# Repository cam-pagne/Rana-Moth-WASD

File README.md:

# The Rana Labs Moth (WASD Version)

WASD version of [Rana Labs'](https://github.com/rana-sylvatica) Moth, a foldable leverless controller.

<div style="display: flex;">
    
</div>

---

## Build Overview (What do I need to make one?)

I printed the entire shell, hinges, etc., in **Bambu Lab Matte PLA** (though any PLA should work, build quality feel may vary).

- **Mainboards:** RP2040—**integrated directly onto the left custom PCB.** The right side is connnected by ribbon cable.
- **Switches:** Must be **low profile switches.** I use pretty much any Kailh Choc Low Profile switches. They all work, just choose a preferred switch type.
- **USB-C Connector:** [Quark's](https://github.com/quark-works) and Rana Labs' [QuRB](https://github.com/rana-sylvatica/rana-tadpole/tree/main/PCBs/Breakout%20Board%20(QuRB)), a USB C Breakout board with a ribbon cable port, for solderless assembly.
- **Hardware:** M2 screws and M3 screws are the only fasteners required to assemble. You will need **ten M3 heat inserts** for the backplates, **twelve M3 x 5/6mm bolts** for the backplates and QuRB, and **eight M2 x 4mm bolts** to secure each half of the mainboards.

---

## Assembly

### PCB

To streamline your build, I’ve designed a custom PCB for this controller. This board integrates the Pico directly eliminating the need for any handwiring of the microcontroller. The **only soldering required is the installation of the hotswap sockets for the Choc switches.**

The two halves of the board are connected using a 20 pin, .5 pitch ribbon cable, and the QuRB is connected to the Left side board for USB C port via a 12 pin, .5 pitch ribbon cable.

---

## Magnets

Strong magnets are crucial, as they must counteract every spring in your switches. I used:

- **6x3mm Neodymium magnets**, stacked **2 high** in each of the **10 total holes** (20 magnets overall).
- This setup creates a satisfying snap and keeps the Moth securely folded.

**Amazon link:** [Magnets used](https://www.amazon.com/dp/B096LZNZTQ?ref=cm_sw_r_cp_ud_dp_ZEAK3BD945P57Y9BB6P4&ref_=cm_sw_r_cp_ud_dp_ZEAK3BD945P57Y9BB6P4&social_share=cm_sw_r_cp_ud_dp_ZEAK3BD945P57Y9BB6P4&skipTwisterOG=1&newOGT=1&th=1)

---

## 'Prism' Ergonomic Mode

For the reverse folded position:

- A **lip** on the two hinge pieces prevents overfolding by creating a defined stopping point.
- The rounded back of the hinges generates friction, ensuring rigidity in the ergonomic 'prism' configuration.

### Adjustments:

- The hinge lip’s width can be edited to modify the folding angle.

---

## Miscellaneous Notes

- **Button Fit:** Ensure buttons sit flush with the face surface when pressed to allow proper folding.
- **Magnet Strength:** Although strong neodymium magnets can overcome minor misalignments, aim for a flush fit.
- **Hinge Pin Slot:** While you can add caps for a cleaner look, the friction fit alone holds securely.

---

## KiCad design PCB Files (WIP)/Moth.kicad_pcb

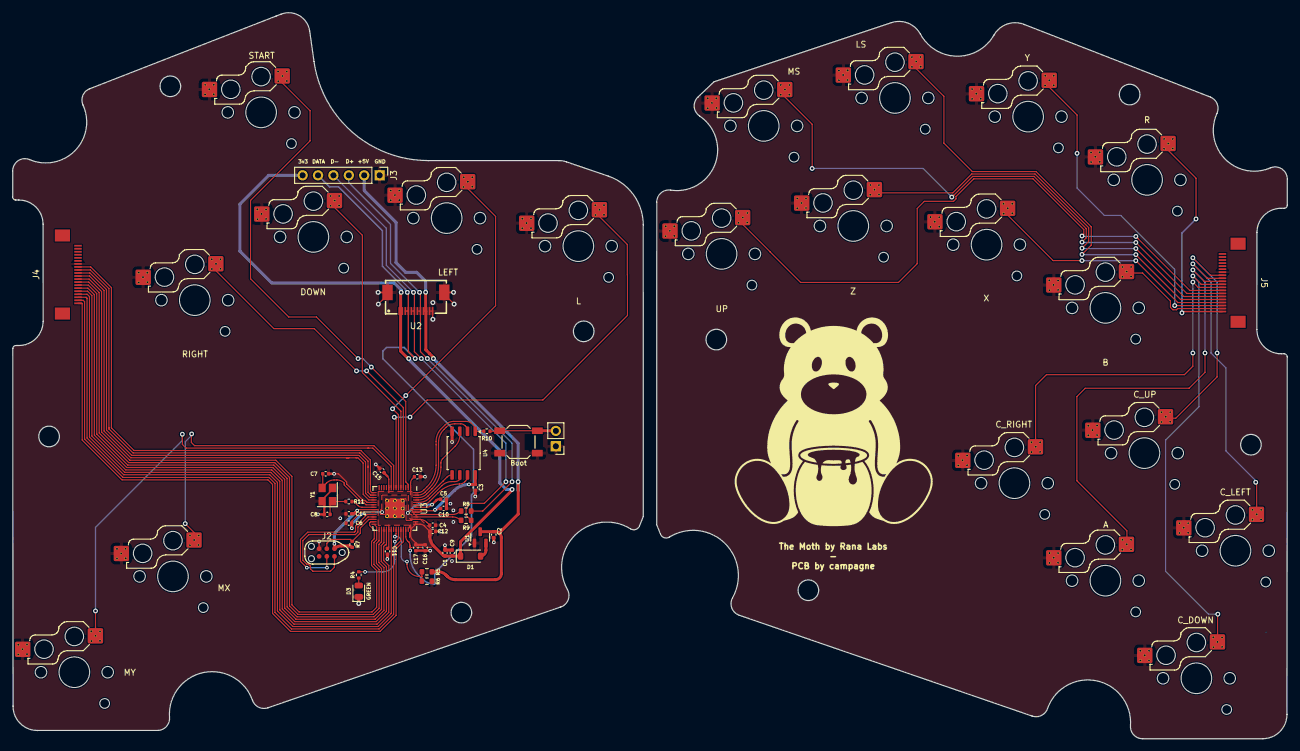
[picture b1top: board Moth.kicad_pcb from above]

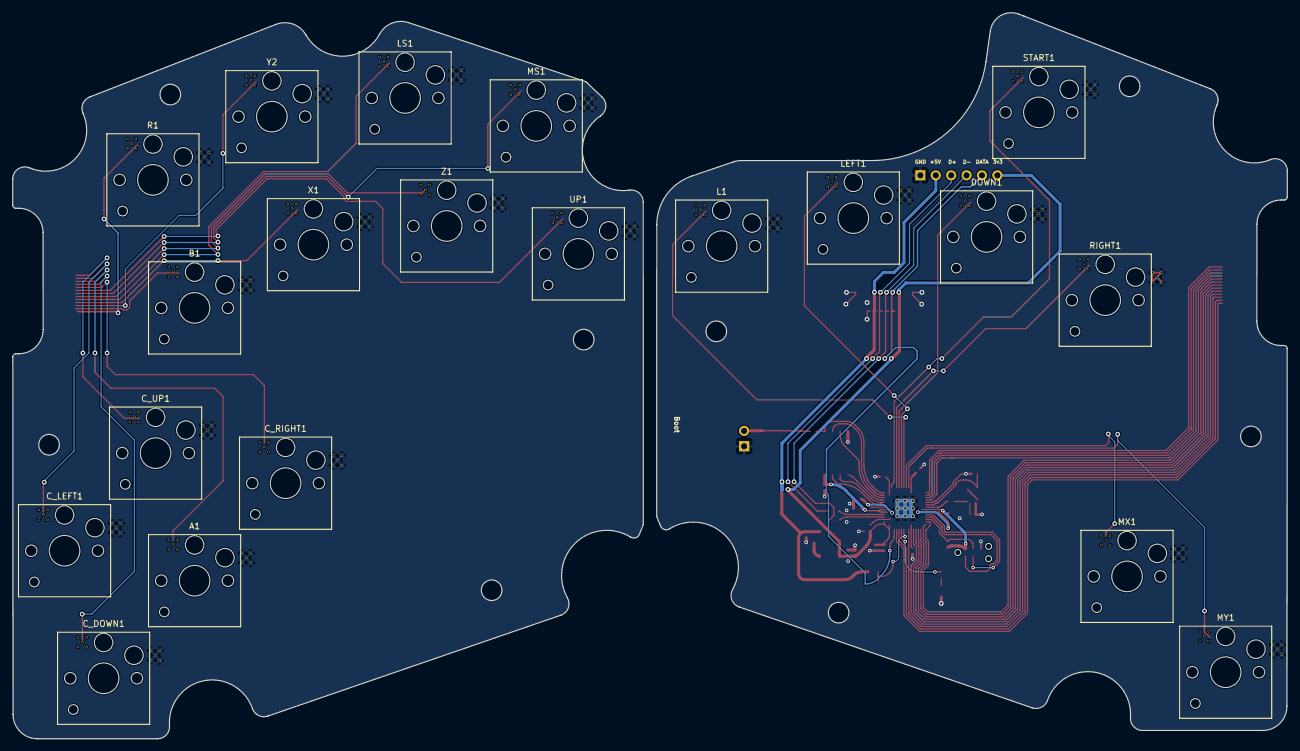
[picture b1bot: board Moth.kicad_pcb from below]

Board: 2 copper layers, 210.2 x 119.7 mm, 58 parts (20 on the bottom side), 59 nets.

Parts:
A1: A; SW_Hotswap_Kailh_Choc_V1V2_THT
B1: B; SW_Hotswap_Kailh_Choc_V1V2_THT
C1, C2, C4, C10: 1uF; C_0402_1005Metric
C3, C5, C6, C11, C12, C13, C14, C15, C16, C17: 100nF; C_0402_1005Metric
C7, C8: 22pF; C_0402_1005Metric
C9: 10uF; C_0402_1005Metric
C_DOWN1: C Down; SW_Hotswap_Kailh_Choc_V1V2_THT
C_LEFT1: C Left; SW_Hotswap_Kailh_Choc_V1V2_THT
C_RIGHT1: C Right; SW_Hotswap_Kailh_Choc_V1V2_THT
C_UP1: C Up; SW_Hotswap_Kailh_Choc_V1V2_THT
D1: Schottky Diode; D_SOD-123
D3: GREEN; LED_0805_2012Metric
DOWN1: Down; SW_Hotswap_Kailh_Choc_V1V2_THT
J1: Conn_01x02; PinHeader_1x02_P2.54mm_Vertical
J2: JTAG_TC2030; CON_TC2030_outlined
J3: DuPont Connector; PinHeader_1x06_P2.54mm_Vertical
J4: Left Ribbon; FPC-05F-30PH20
J5: Right Ribbon; FPC-05F-30PH20
L1: L; SW_Hotswap_Kailh_Choc_V1V2_THT
LEFT1: Left; SW_Hotswap_Kailh_Choc_V1V2_THT
LS1: LS; SW_Hotswap_Kailh_Choc_V1V2_THT
MS1: MS; SW_Hotswap_Kailh_Choc_V1V2_THT
MX1: MX; SW_Hotswap_Kailh_Choc_V1V2_THT
MY1: MY; SW_Hotswap_Kailh_Choc_V1V2_THT
R1: R; SW_Hotswap_Kailh_Choc_V1V2_THT
R4: 470; R_0402_1005Metric
R5: 5.6k; R_0603_1608Metric
R6: 10k; R_0603_1608Metric
R7: 10k; R_0402_1005Metric
R8, R9: 27; R_0603_1608Metric
R10, R11: 1k; R_0402_1005Metric
RIGHT1: Right; SW_Hotswap_Kailh_Choc_V1V2_THT
START1: Start; SW_Hotswap_Kailh_Choc_V1V2_THT
SW1: Boot; SW_SPST_SKQG_WithStem
U1: XC6206; SOT-23
U2: X05A26H12G; FPC-SMD_X05A26H12G
U3: RP2040; RP2040-QFN-56
U4: W25Q128JVS; SOIC-8_5.23x5.23mm_P1.27mm
UP1: Up; SW_Hotswap_Kailh_Choc_V1V2_THT
X1: X; SW_Hotswap_Kailh_Choc_V1V2_THT
Y1: 12MHz; Crystal_SMD_3225-4Pin_3.2x2.5mm
Y2: Y; SW_Hotswap_Kailh_Choc_V1V2_THT
Z1: Z; SW_Hotswap_Kailh_Choc_V1V2_THT

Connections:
3vDiode: C1.2, C3.1, C9.1, C10.1, C11.1, C12.1, C13.1, C14.1, C15.1, C16.1, C17.1, D1.1 (K), J2.1 (VCC), J3.6, R7.1, U2.1, U2.2, U3.1 (IOVDD), U3.10 (IOVDD), U3.22 (IOVDD), U3.33 (IOVDD), U3.42 (IOVDD), U3.43 (ADC_AVDD), U3.44 (VREG_VIN), U3.48 (USB_VDD), U3.49 (IOVDD), U4.8 (VCC)
+1V1: C4.1, C5.1, C6.1, U3.23 (DVDD), U3.45 (VREG_VOUT), U3.50 (DVDD)
+5V: C2.2, J3.2, R5.1, U1.3 (VI), U2.9, U2.10
/D_+: R8.2, U3.47 (D+)
/D_-: R9.2, U3.46 (D-)
/XTAL_O: C8.2, R11.1, Y1.1
/~USB_BOOT: J1.2, R10.1, SW1.2
A: A1.1, J5.11
A RIBBON: J4.10, U3.17 (GPIO14)
B: B1.1, J5.2
B RIBBON: J4.19, U3.38 (GPIO26/ADC0)
CS: R10.2, U3.56 (QSPI_SS_N), U4.1 (~CS)
C_DN: C_DOWN1.1, J5.10
C_DN RIBBON: J4.11, U3.18 (GPIO15)
C_LT: C_LEFT1.1, J5.12
C_LT RIBBON: J4.9, U3.16 (GPIO13)
C_RT: C_RIGHT1.1, J5.9
C_RT RIBBON: J4.12, U3.27 (GPIO16)
C_UP: C_UP1.1, J5.13
C_UP RIBBON: J4.8, U3.15 (GPIO12)
D+: J3.3, R8.1, U2.7, U2.8
D-: J3.4, R9.1, U2.5, U2.6
DATA: J3.5, U2.3, U2.4, U3.40 (GPIO28/ADC2)
DOWN: DOWN1.1, U3.5 (GPIO3)
GND: A1.2, B1.2, C1.1, C2.1, C3.2, C4.2, C5.2, C6.2, C7.1, C8.1, C9.2, C10.2, C11.2, C12.2, C13.2, C14.2, C15.2, C16.2, C17.2, C_DOWN1.2, C_LEFT1.2, C_RIGHT1.2, C_UP1.2, D3.1 (K), DOWN1.2, J1.1, J2.5 (GND), J3.1, J4.7, J5.14, L1.2, LEFT1.2, LS1.2, MS1.2, MX1.2, MY1.2, R1.2, R6.2, RIGHT1.2, START1.2, SW1.1, U1.1 (GND), U2.11, U2.12, U2.13, U2.14, U3.19 (TESTEN), U3.57 (GND), U4.4 (GND), UP1.2, X1.2, Y1.2, Y1.4, Y2.2, Z1.2
L: L1.1, U3.7 (GPIO5)
LEFT: LEFT1.1, U3.6 (GPIO4)
LS: J5.5, LS1.1
LS RIBBON: J4.16, U3.31 (GPIO20)
M1: MX1.1, U3.8 (GPIO6)
M2: MY1.1, U3.9 (GPIO7)
MS: J5.7, MS1.1
MS RIBBON: J4.14, U3.29 (GPIO18)
unnamed: D1.2 (A), U1.2 (VO)
unnamed: D3.2 (A), R4.2
PICO_LED: R4.1, U3.37 (GPIO25)
QSPI_CLK: U3.52 (QSPI_SCLK), U4.6 (CLK)
R: J5.1, R1.1
R RIBBON: J4.20, U3.39 (GPIO27/ADC1)
RIGHT: RIGHT1.1, U3.4 (GPIO2)
SD0: U3.53 (QSPI_SD0), U4.5 (DI(IO0))
SD1: U3.55 (QSPI_SD1), U4.2 (DO(IO1))
SD2: U3.54 (QSPI_SD2), U4.3 (IO2)
SD3: U3.51 (QSPI_SD3), U4.7 (IO3)
START: START1.1, U3.2 (GPIO0)
SWCLK: J2.4 (SWCLK), U3.24 (SWCLK)
SWD: J2.2 (SWDIO), U3.25 (SWDIO)
UP: J5.8, UP1.1
UP RIBBON: J4.13, U3.28 (GPIO17)
VBUS_SENSE: R5.2, R6.1, U3.36 (GPIO24)
X: J5.4, X1.1
X RIBBON: J4.17, U3.32 (GPIO21)
XTAL_IN: C7.2, U3.20 (XTAL_IN), Y1.3
XTAL_OUT: R11.2, U3.21 (XTAL_OUT)
Y: J5.3, Y2.1
Y RIBBON: J4.18, U3.34 (GPIO22)
Z: J5.6, Z1.1
Z RIBBON: J4.15, U3.30 (GPIO19)
~RESET: J2.3 (~RST), R7.2, U3.26 (~RUN)

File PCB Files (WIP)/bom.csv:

Designator,Footprint,Quantity,Value,LCSC Part #
"C1, C10, C2, C4",402,4,1uF,C52923
"C11, C12, C13, C14, C15, C16, C17, C3, C5, C6",402,10,100nF,C1525
"C7, C8",402,2,22pF,C1555
C9,402,1,10uF,C15525
D1,D_SOD-123,1,Schottky Diode,C8598
D3,805,1,RED,C84256
"R10, R11",402,2,1k,C11702
R4,402,1,470,C25117
R5,603,1,5.6k,C23189
R6,603,1,10k,C25804
R7,402,1,10k,C25744
"R8, R9",RP2040-QFN-56,2,27,C25190
SW1,SW_SPST_SKQG_WithStem,1,Boot,C318884 
U1,SOT-23,1,XC6206,C5446
U2,FPC-SMD_X05A26H12G,1,X05A26H12G,C519263
U3,RP2040-QFN-56,1,RP2040,C2040
U4,SOIC-8_5.23x5.23mm_P1.27mm,1,W25Q128JVS,C97521
Y1,Crystal_SMD_3225-4Pin_3.2x2.5mm,1,12MHz,C9002
"J4, J5",XUNPU FPC-05F-20PH20,2,FPC-05F-20PH20,C2856803

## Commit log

2025-01-20 Create f
2025-01-21 Add files via upload
    Increased the size of the bottom hinge to add more friction in prism mode
2025-01-22 Added DXF files for PCB creation.
2025-01-22 Added DXFs for the possible creation of a PCB for the Moth.
2025-01-23 Folder creation
2025-01-23 new folder
2025-01-24 Reconfigured PCB, closer to completion.
2025-01-25 Completed PCB pending review
2025-01-29 PCB files possibly done pending testing
2025-02-24 Create A
